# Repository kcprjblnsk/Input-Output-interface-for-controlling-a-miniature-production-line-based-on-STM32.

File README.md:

# Input-Output-interface-for-controlling-a-miniature-production-line-based-on-STM32. // Interfejs Wejść/Wyjść Mikrokontrolera do STM32F429 DISCOVERY w celu sterowania miniaturową linią produkcyjną 

Ten projekt ma na celu zintegrowanie mikrokontrolera STM32F429 DISCOVERY z interfejsem wejść/wyjść w celu oddzielenia sygnałów, połączeń elektrycznych i sterowania elementami wykonawczymi w prototypie miniaturowej linii produkcyjnej.

## Przegląd Projektu

Projekt wykorzystuje płytę STM32F429 DISCOVERY jako główny komponent do sterowania linią produkcyjną. Dzięki połączeniu z własnym interfejsem Wejście/Wyjście, udaje się izolować różne sygnały i połączenia elektryczne, co gwarantuje efektywne zarządzanie i sterowanie elementami linii produkcyjnej.

## Konfiguracja Sprzętu

Płytę STM32F429 DISCOVERY wpina się w interfejs, wykorzystując do tego dwa, dwurzędowe, 64-pinowe złącza. Wszystkie sygnały i napięcia układu są do niego doprowadzone. W tym celu zastosowano złącza 4-, 14- i 18-pinowe, co zapewnia łatwe utrzymanie systemu.

## Utrzymanie

Ta konstrukcja zapewnia prosty sposób na serwisowanie systemu dzięki łatwo dostępnym i modularnym złączom. Wszelkie wymagane naprawy lub modyfikacje systemu mogą być przeprowadzane szybko i sprawnie.

## Wnioski

Projekt oferuje eleganckie rozwiązanie do sterowania miniaturową linią produkcyjną przy użyciu wszechstronnego mikrokontrolera STM32F429 DISCOVERY. Oferuje to doskonałą skalowalność dla projektów tego typu i otwiera drzwi do wielu możliwości dalszego rozwoju i rozbudowy.

## Licencja

Ten projekt jest objęty [licencją MIT](LICENSE) (jeśli dotyczy).

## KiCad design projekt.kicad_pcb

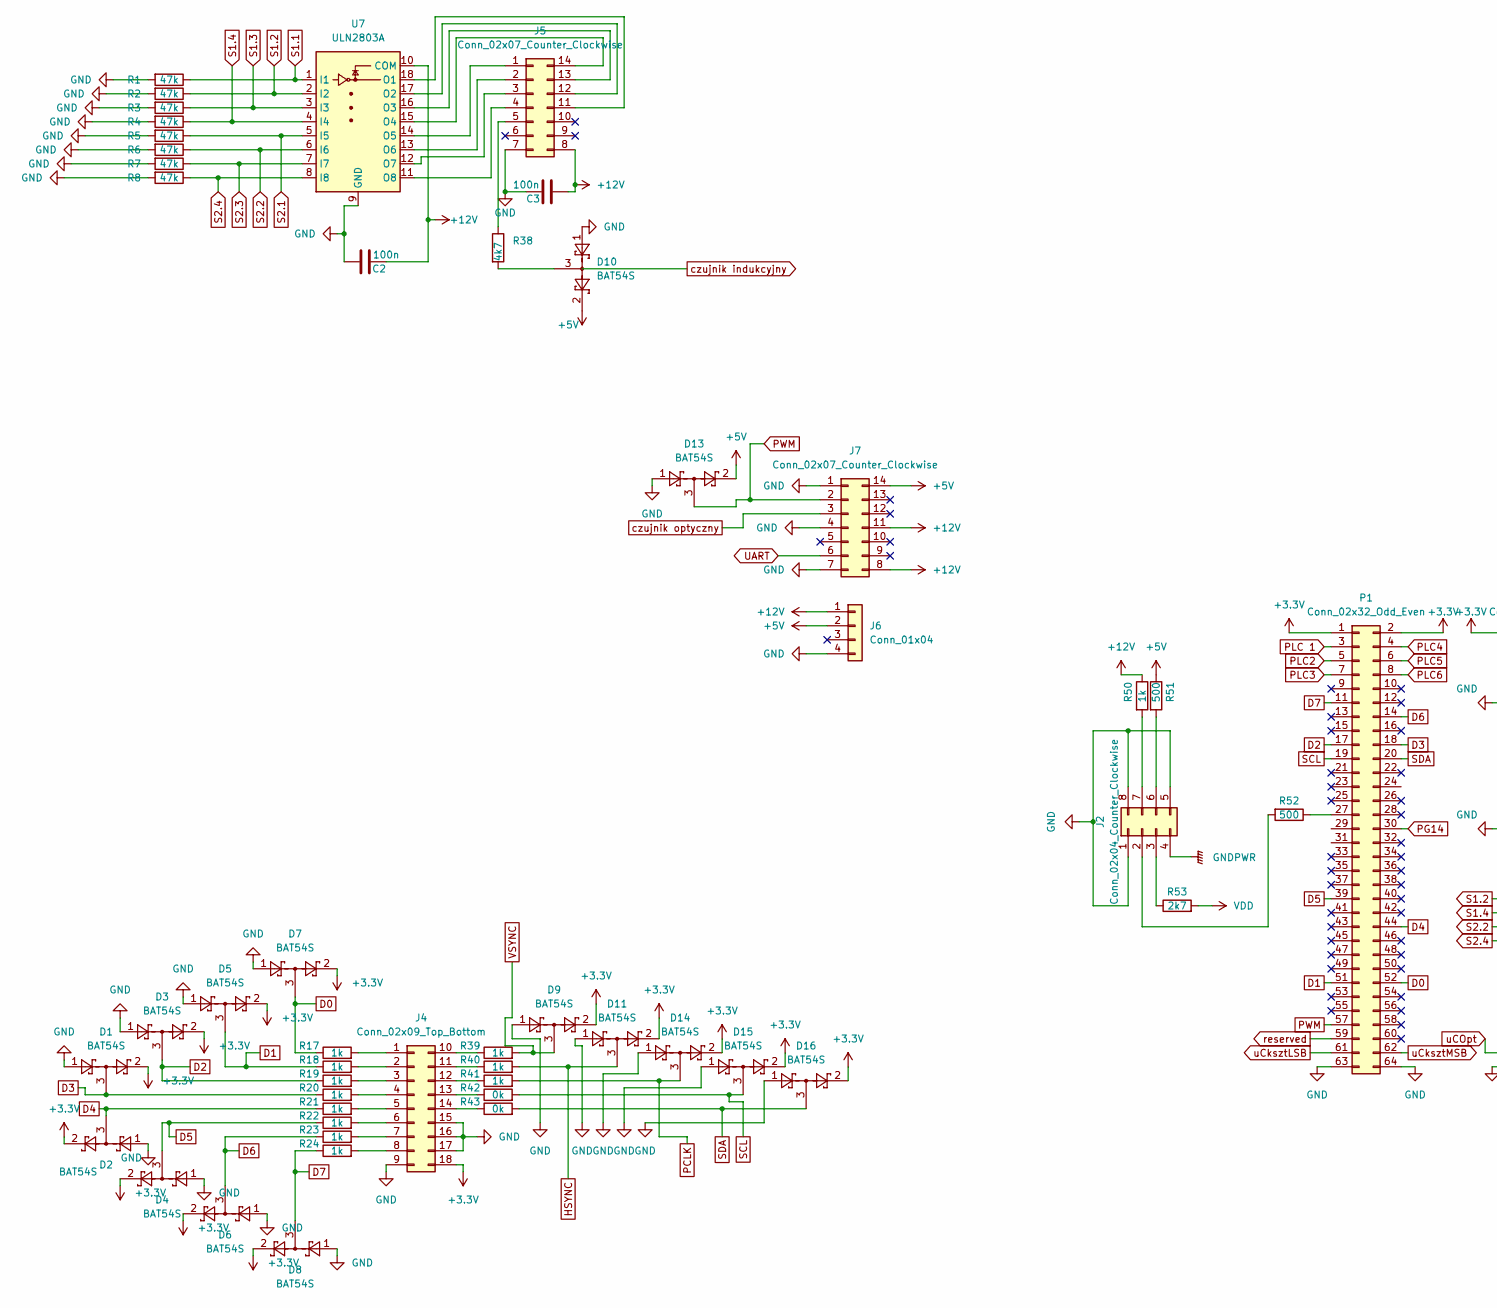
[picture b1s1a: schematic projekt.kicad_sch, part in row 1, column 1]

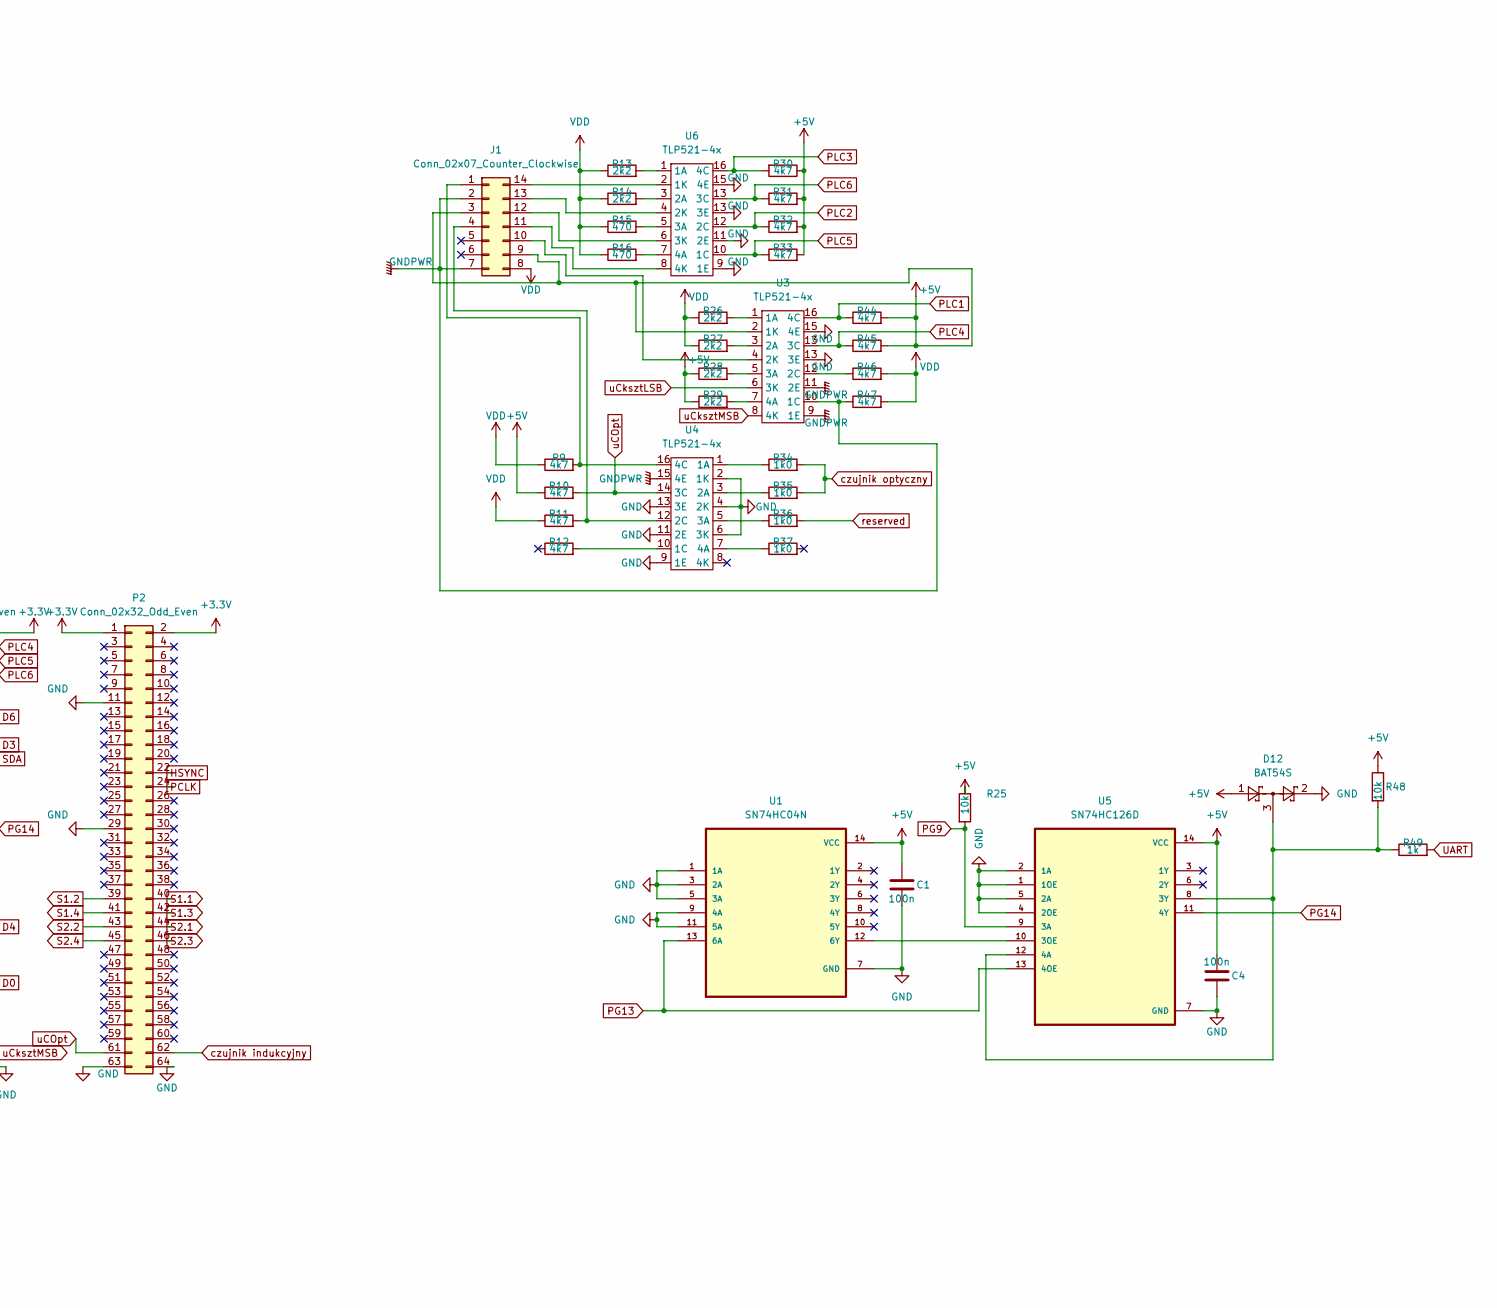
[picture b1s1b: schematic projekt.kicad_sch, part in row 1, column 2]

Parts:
C1, C2, C3, C4: 100n; C_0805_2012Metric
D1, D2, D3, D4, D5, D6, D7, D8, D9, D10, D11, D12, D13, D14, D15, D16: BAT54S; SOT-23
J1, J5, J7: Conn_02x07_Counter_Clockwise; Molex_Micro-Fit_3.0_43045-1412_2x07_P3.00mm_Vertical
J2: Conn_02x04_Counter_Clockwise; PinSocket_2x04_P2.54mm_Vertical
J4: Conn_02x09_Top_Bottom; Molex_Micro-Fit_3.0_43045-1812_2x09_P3.00mm_Vertical
J6: Conn_01x04; Molex_Micro-Latch_53253-0470_1x04_P2.00mm_Vertical
P1, P2: Conn_02x32_Odd_Even; PinSocket_2x32_P2.54mm_Vertical
R1, R2, R3, R4, R5, R6, R7, R8: 47k; R_0805_2012Metric
R9, R10, R11, R12, R30, R31, R32, R33, R38, R44, R45, R46, R47: 4k7; R_0805_2012Metric
R13, R14, R26, R27, R28, R29: 2k2; R_0805_2012Metric
R15, R16: 470; R_0805_2012Metric
R17, R18, R19, R20, R21, R22, R23, R24, R39, R40, R41, R49, R50: 1k; R_0805_2012Metric
R25, R48: 10k; R_0805_2012Metric
R34, R35, R36, R37: 1k0; R_0805_2012Metric
R42, R43: 0k; R_0805_2012Metric
R51, R52: 500; R_0805_2012Metric
R53: 2k7; R_0805_2012Metric
U1: SN74HC04N; DIP-14_W7.62mm
U3, U4, U6: TLP521-4x; DIP-16_W7.62mm
U5: SN74HC126D; DIP-14_W7.62mm
U7: ULN2803A; DIP-18_W7.62mm

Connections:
+3.3V: D1.2, D2.2, D3.2, D4.2, D5.2, D6.2, D7.2, D8.2, D9.2, D11.2, D14.2, D15.2, D16.2, J4.18, P1.1, P1.2, P2.1, P2.2
+5V: C1.1, C4.2, D10.2, D12.1, D13.2, J1.3, J1.9, J6.2, J7.14, R10.1, R25.1, R28.1, R29.1, R30.1, R31.2, R32.2, R33.2, R44.2, R45.2, R48.1, R51.1, U1.14 (VCC), U3.2 (1K), U5.14 (VCC)
+12V: C2.2, C3.2, J5.8, J6.1, J7.8, J7.11, R50.1, U7.10 (COM)
D0: D7.3, P1.52, R17.1
D1: D5.3, P1.51, R18.1
D2: D3.3, P1.17, R19.1
D3: D1.3, P1.18, R20.1
D4: D2.3, P1.44, R21.1
D5: D4.3, P1.39, R22.1
D6: D6.3, P1.14, R23.1
D7: D8.3, P1.11, R24.1
GNDPWR: J1.2, J1.7, J2.4, R47.1, U3.9 (1E), U3.10 (1C), U3.11 (2E), U4.15 (4E)
HSYNC: D11.3, P2.22, R40.2
unnamed: D10.3, R38.2
unnamed: D12.3, R48.2, R49.1, U5.8 (3Y), U5.12 (4A)
unnamed: J1.1, R9.2, U4.16 (4C)
unnamed: J1.4, R11.2, U4.12 (2C)
unnamed: J1.10, U3.4 (2K)
unnamed: J1.11, U6.8 (4K)
unnamed: J1.12, U6.6 (3K)
unnamed: J1.13, U6.4 (2K)
unnamed: J1.14, U6.2 (1K)
unnamed: J2.2, R52.2
unnamed: J2.3, R53.1
unnamed: J2.6, R51.2
unnamed: J2.7, R50.2
unnamed: J4.1, R17.2
unnamed: J4.2, R18.2
unnamed: J4.3, R19.2
unnamed: J4.4, R20.2
unnamed: J4.5, R21.2
unnamed: J4.6, R22.2
unnamed: J4.7, R23.2
unnamed: J4.8, R24.2
unnamed: J4.10, R39.1
unnamed: J4.11, R40.1
unnamed: J4.12, R41.1
unnamed: J4.13, R42.1
unnamed: J4.14, R43.1
unnamed: J5.1, U7.14 (O5)
unnamed: J5.2, U7.13 (O6)
unnamed: J5.3, U7.12 (O7)
unnamed: J5.4, U7.11 (O8)
unnamed: J5.5, R38.1
unnamed: J5.11, U7.18 (O1)
unnamed: J5.12, U7.17 (O2)
unnamed: J5.13, U7.16 (O3)
unnamed: J5.14, U7.15 (O4)
unnamed: P1.27, R52.1
unnamed: R12.2, U4.10 (1C)
unnamed: R13.2, U6.1 (1A)
unnamed: R14.2, U6.3 (2A)
unnamed: R15.2, U6.5 (3A)
unnamed: R16.2, U6.7 (4A)
unnamed: R26.2, U3.1 (1A)
unnamed: R27.2, U3.3 (2A)
unnamed: R28.2, U3.5 (3A)
unnamed: R29.2, U3.7 (4A)
unnamed: R34.1, U4.1 (1A)
unnamed: R35.1, U4.3 (2A)
unnamed: R36.1, U4.5 (3A)
unnamed: R37.1, U4.7 (4A)
unnamed: R46.1, U3.12 (2C)
unnamed: U1.12 (6Y), U5.10 (3OE)
PCLK: D14.3, P2.24, R41.2
PG9: R25.2, U5.9 (3A)
PG13: U1.13 (6A), U5.13 (4OE)
PG14: P1.30, U5.11 (4Y)
PLC1: R44.1, U3.16 (4C)
PLC2: P1.5, R32.1, U6.12 (2C)
PLC3: P1.7, R30.2, U6.16 (4C)
PLC5: P1.6, R33.1, U6.10 (1C)
PLC 1: P1.3
PWM: D13.3, J7.2, P1.57
S1.1: P2.40, R1.1, U7.1 (I1)
S1.2: P2.39, R2.1, U7.2 (I2)
S1.3: P2.42, R3.1, U7.3 (I3)
S1.4: P2.41, R4.1, U7.4 (I4)
S2.1: P2.44, R5.1, U7.5 (I5)
S2.2: P2.43, R6.1, U7.6 (I6)
S2.3: P2.46, R7.1, U7.7 (I7)
S2.4: P2.45, R8.1, U7.8 (I8)
SCL: D15.3, P1.19, R42.2
SDA: D16.3, P1.20, R43.2
UART: J7.6, R49.2
VDD: J1.8, R9.1, R11.1, R13.1, R14.1, R15.1, R16.1, R26.1, R27.1, R46.2, R47.2, R53.2
VSYNC: D9.3, R39.2
czujnik indukcyjny: P2.62
czujnik optyczny: J7.3, R34.2, R35.2
reserved: P1.59, R36.2
uCOpt: P2.61, R10.2, U4.14 (3C)
uCksztLSB: P1.61, U3.6 (3K)
uCksztMSB: P1.62, U3.8 (4K)

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
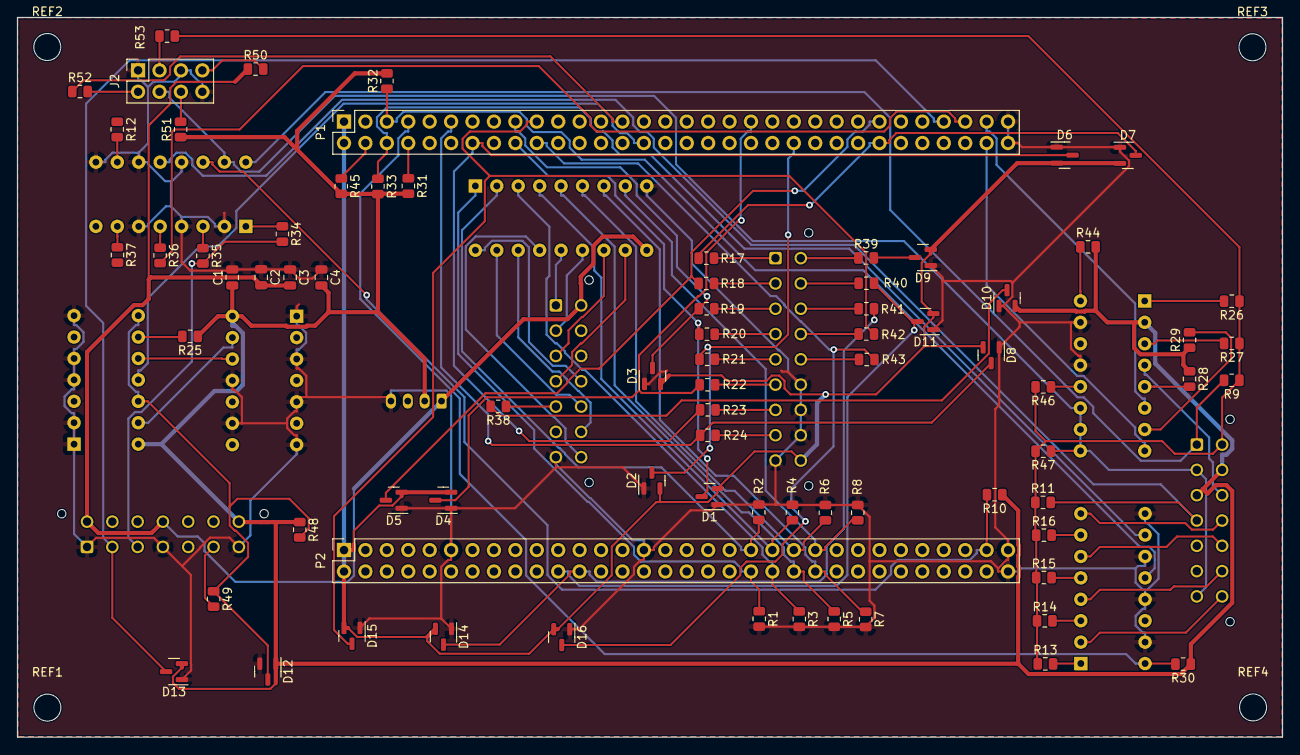
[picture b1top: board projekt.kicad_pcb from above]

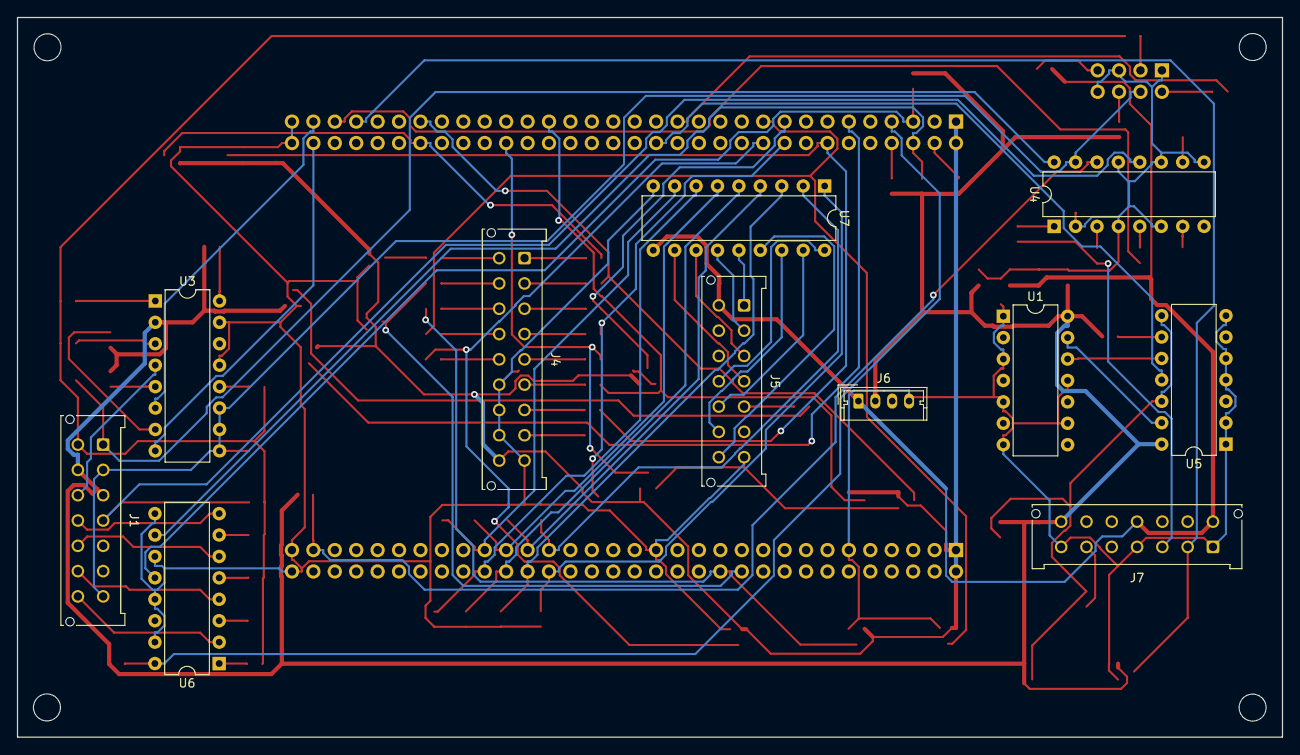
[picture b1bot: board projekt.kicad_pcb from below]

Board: 2 copper layers, 150.0 x 85.3 mm, 91 parts (11 on the bottom side), 94 nets.

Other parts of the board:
REF1, REF2, REF3, REF4: MountingHole_3.2mm_M3

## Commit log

2023-06-01 Added LICENSE
